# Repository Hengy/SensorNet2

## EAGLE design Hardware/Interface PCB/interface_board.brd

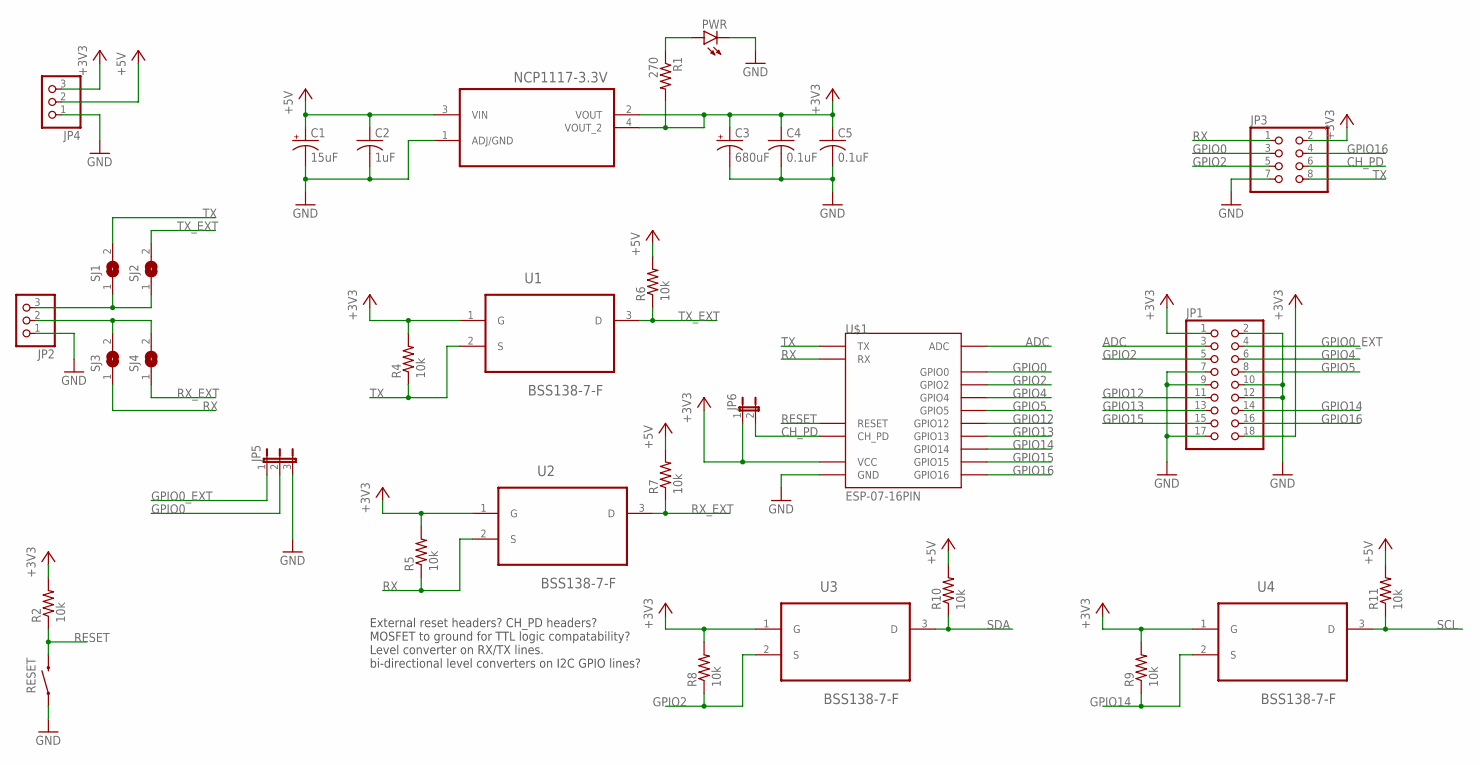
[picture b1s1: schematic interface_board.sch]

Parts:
C1: 15uF; E2-5
C2: 1uF; C1206
C3: 680uF; E5-10,5
C4, C5: 0.1uF; C1206
JP1: PINHD-2X9/90; 2X09/90
JP2, JP4: PINHD-1X3; 1X03
JP3: PINHD-2X4; 2X04
JP5: JP2E; JP2
JP6: JP1E; JP1
NCP1117-3.3V: LM1117IMP-5.0; SOT230P696X180-4N
PWR: PURPLE; LED-1206
R1: 270; R1206
R2, R4, R5, R6, R7, R8, R9, R10, R11: 10k; R1206
RESET: SWITCH-MOMENTARY-2SMD-REDUNDANT; TACTILE-SWITCH-SMD
SJ1, SJ2, SJ3, SJ4: SJ
U1, U2, U3, U4: BSS138-7-F; SOT95P240X110-3N
U$1: ESP-07-16PIN

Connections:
+3V3: C3.+, C4.1, C5.1, JP1.1, JP1.18, JP3.2, JP4.3, JP6.1, NCP1117-3.3V.2 (VOUT), NCP1117-3.3V.4 (VOUT_2), R1.2, R2.2, R4.2, R5.2, R8.2, R9.2, U1.1 (G), U2.1 (G), U3.1 (G), U4.1 (G), U$1.VCC
+5V: C1.+, C2.1, JP4.2, NCP1117-3.3V.3 (VIN), R6.2, R7.2, R10.2, R11.2
ADC: JP1.3, U$1.ADC
CH_PD: JP3.6, JP6.2, U$1.CH_PD
GND: C1.-, C2.2, C3.-, C4.2, C5.2, JP1.2, JP1.7, JP1.9, JP1.10, JP1.12, JP1.17, JP2.1, JP3.7, JP4.1, JP5.3, NCP1117-3.3V.1 (ADJ/GND), PWR.C, RESET.1, RESET.2 (1), U$1.GND
GPIO0: JP3.3, JP5.2, U$1.GPIO0
GPIO0_EXT: JP1.4, JP5.1
GPIO2: JP1.5, JP3.5, R8.1, U3.2 (S), U$1.GPIO2
GPIO4: JP1.6, U$1.GPIO4
GPIO5: JP1.8, U$1.GPIO5
GPIO12: JP1.11, U$1.GPIO12
GPIO13: JP1.13, U$1.GPIO13
GPIO14: JP1.14, R9.1, U4.2 (S), U$1.GPIO14
GPIO15: JP1.15, U$1.GPIO15
GPIO16: JP1.16, JP3.4, U$1.GPIO16
unnamed: PWR.A, R1.1
unnamed: JP2.3, SJ1.1, SJ2.1
unnamed: JP2.2, SJ3.2, SJ4.2
RESET: R2.1, RESET.3 (2), RESET.4 (2), U$1.REST (RESET)
RX: JP3.1, R5.1, SJ3.1, U2.2 (S), U$1.RX
RX_EXT: R7.1, SJ4.1, U2.3 (D)
SCL: R11.1, U4.3 (D)
SDA: R10.1, U3.3 (D)
TX: JP3.8, R4.1, SJ1.2, U1.2 (S), U$1.TX
TX_EXT: R6.1, SJ2.2, U1.3 (D)

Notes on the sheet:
External reset headers? CH_PD headers? MOSFET to ground for TTL logic compatability? Level converter on RX/TX lines. bi-directional level converters on I2C GPIO lines?

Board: 2 copper layers, 33 parts (0 on the bottom side), 25 nets, no tracks yet.

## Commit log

2015-06-29 :tada: Added .gitattributes & .gitignore files
2015-06-29 Interface board design
    Started design of interface board. Includes 3.3v regulator, RX/TX level
    converters, reset button, program button, solder pads for ESP-07 and
    ESP-12, headers for other ESP modules, and breakout header for
    ESP-07/ESP-12 GPIO pins.
2015-06-30 Interface board
2015-07-15 Main program
    Added config file parser using ConfigParse, command-line parser using
    argparse, logging, and signal handling. Finished UDP service discovery
    process.
2015-07-15 Added python files
    See previous commit
2015-07-15 Updated git ignore file. added Eclipse project files
2015-07-15 changed file names to make Linux navigation easier
2015-07-15 Deleted duplicate content
2015-07-15 Multicast group membership code
2015-07-15 Added required local ip argument
2015-07-15 Removed arg string from parseArgs() line
2015-07-15 Added .log files to gitignore
2015-07-17 Added error handling for socket and select system calls
2015-07-17 Added node simulation script

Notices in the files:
parts and their libraries:
SparkFun-LED: Licensing: Creative Commons ShareAlike 4.0 International - https://creativecommons.org/licenses/by-sa/4.0
